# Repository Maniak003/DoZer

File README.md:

<!DOCTYPE html>
<html lang="en" data-color-mode="auto" data-light-theme="light" data-dark-theme="dark">
  <head>
    <meta charset="utf-8">
  </head>
    <body class="logged-in env-production page-responsive page-blob" style="word-wrap: break-word;">
      <a href="https://play.google.com/store/apps/details?id=ru.starline.dozer" rel="nofollow">Application download</a>
      <p> DoZer Scintillation gamma spectrometer based on SiPM Sensl FC60035/FJ60035, Broadcom AFBR-S4N66C013 & NaI(Tl) or SrI2(Eu).</p>
      
      <a href="https://github.com/Maniak003/DoZer/wiki/Description" rel="nofollow">Description</a>
    </body>
</html>

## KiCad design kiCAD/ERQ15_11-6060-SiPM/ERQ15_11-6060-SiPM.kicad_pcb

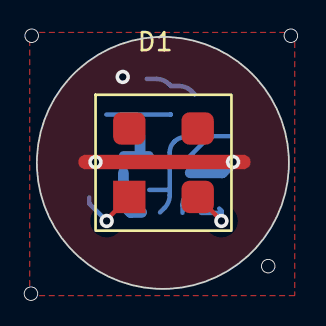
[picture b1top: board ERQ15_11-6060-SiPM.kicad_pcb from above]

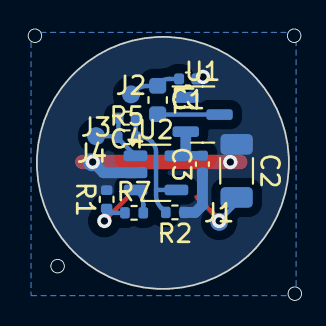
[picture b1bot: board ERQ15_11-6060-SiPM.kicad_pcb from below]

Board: 2 copper layers, 14.0 x 14.0 mm, 16 parts (15 on the bottom side), 9 nets.

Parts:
C1, C3: 10u; C_0402_1005Metric
C2: 10u; C_1206_3216Metric
C4: 2p; C_0402_1005Metric
D1: EQR15-11-6060D-S; EQR15_11-6060D-S
J1, J2, J3, J4: Conn; conn_mini
L1: 47uH; L_0603_1608Metric
R1: 1k; R_0402_1005Metric
R2, R7: 10k; R_0402_1005Metric
R5: 100k; R_0402_1005Metric
U1: MCP1700x-280xxTT; SOT-23
U2: OPA354; SOT-23-5

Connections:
+3V0: C3.2, U1.2 (VO), U2.5 (V+)
GND: C1.1, C2.1, C3.1, J4.1, R1.2, R2.1, U1.1 (GND), U2.2 (V-)
unnamed: C1.2, J2.1, L1.1
unnamed: C4.2, J3.1, R5.1, U2.1
unnamed: D1.2 (A), R1.1, R7.1
unnamed: C2.2, D1.1 (C), J1.1
unnamed: L1.2, U1.3 (VI)
unnamed: R7.2, U2.3 (+)
unnamed: C4.1, R2.2, R5.2, U2.4 (-)

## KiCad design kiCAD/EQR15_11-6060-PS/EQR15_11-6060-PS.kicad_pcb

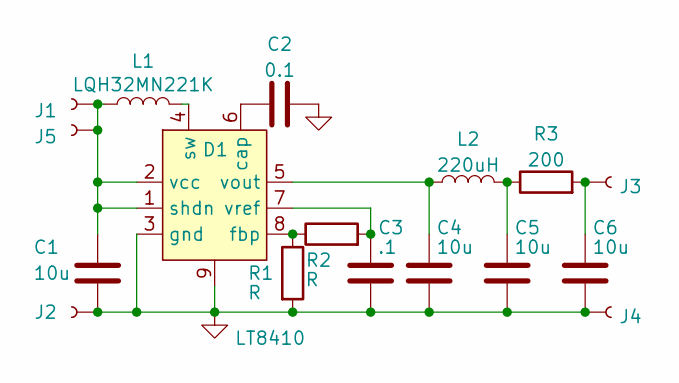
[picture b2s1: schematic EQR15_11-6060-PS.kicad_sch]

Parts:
C1: 10u; C_0402_1005Metric
C2: 0.1; C_0402_1005Metric
C3: .1; C_0402_1005Metric
C4, C5, C6: 10u; C_0805_2012Metric
D1: LT8410; DFN-8-1EP_2x2mm_P0.45mm_EP0.64x1.38mm
J1, J2, J3, J4, J5: Conn; conn_mini
L1: LQH32MN221K; L_1210_3225Metric
L2: 220uH; L_0805_2012Metric
R1, R2: R; R_0402_1005Metric
R3: 200; R_0402_1005Metric

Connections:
GND: C1.2, C2.2, C3.2, C4.2, C5.2, C6.2, D1.3 (gnd), D1.9, J2.1, J4.1, R1.2
unnamed: C1.1, D1.1 (shdn), D1.2 (vcc), J1.1, J5.1, L1.1
unnamed: C2.1, D1.6 (cap)
unnamed: C3.1, D1.7 (vref), R2.2
unnamed: C4.1, D1.5 (vout), L2.1
unnamed: C5.1, L2.2, R3.1
unnamed: C6.1, J3.1, R3.2
unnamed: D1.4 (sw), L1.2
unnamed: D1.8 (fbp), R1.1, R2.1

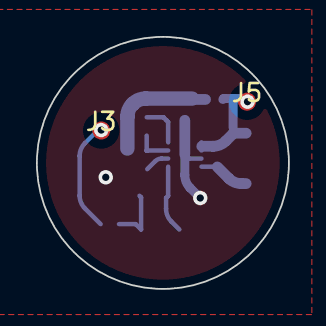
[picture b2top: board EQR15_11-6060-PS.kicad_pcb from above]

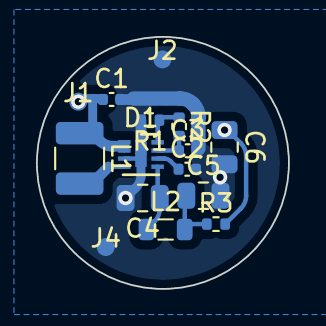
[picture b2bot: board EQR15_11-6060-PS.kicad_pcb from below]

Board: 2 copper layers, 14.0 x 14.0 mm, 17 parts (15 on the bottom side), 9 nets.

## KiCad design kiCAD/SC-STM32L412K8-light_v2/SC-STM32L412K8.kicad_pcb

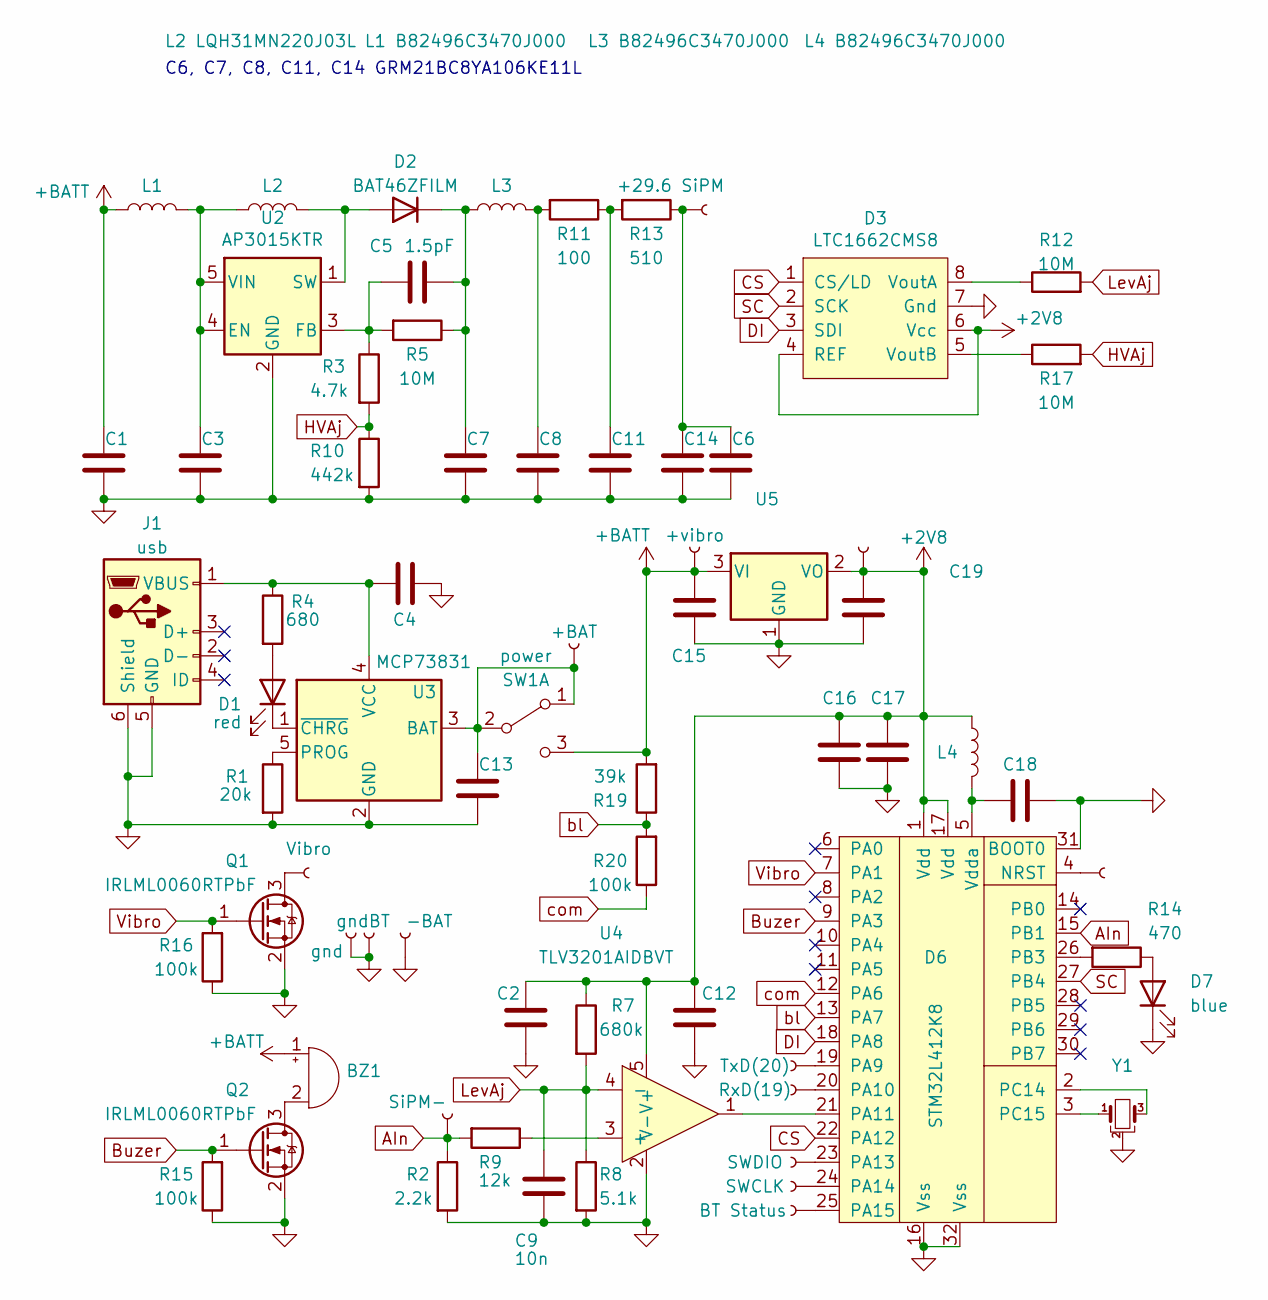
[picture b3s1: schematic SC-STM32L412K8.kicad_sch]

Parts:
BZ1: Buzzer; Buzzer5x5
C1, C2, C3, C4, C13, C15, C16, C17, C19: 1uF; C_0603_1608Metric
C5: 1.5pF; C_0603_1608Metric
C6, C7, C8, C11, C14: GRM21BC8YA106KE11L; C_0805_2012Metric
C9: 10n; C_0402_1005Metric
C12: GRM21BR60J226M; C_0805_2012Metric
C18: GRM21BR60J226M; C_0603_1608Metric
D1: red; LED_0402_1005Metric
D2: BAT46ZFILM; D_SOD-123
D3: LTC1662CMS8; MSOP-8_3x3mm_P0.65mm
D6: STM32L412K8; LQFP-32_7x7mm_P0.8mm
D7: blue; LED_0402_1005Metric
J1: usb; USB_Micro-B_Molex_47346-0001
J2: +29.6 SiPM; SMD-CONN
J3: TxD(20); conn_mini
J4: RxD(19); conn_mini
J5: SWDIO; conn_mini
J6: SWCLK; conn_mini
J7: +BAT; conn_mini
J8: SiPM-; SMD-CONN
J9: BT Status; conn_mini
J10: gnd; conn_mini
J11: Vibro; conn_mini
J12, J16: +2.8v; conn_mini
J13: +vibro; conn_mini
J14: gndBT; SMD-CONN
J15: -BAT; SMD-CONN
L1: L1 B82496C3470J000; L_0603_1608Metric
L2: L2 LQH31MN220J03L; L_1210_3225Metric
L3: L3 B82496C3470J000; L_0603_1608Metric
L4: L4 B82496C3470J000; L_0603_1608Metric
Q1, Q2: IRLML0060RTPbF; SOT-23
R1: 20k; R_0402_1005Metric
R2: 2.2k; R_0402_1005Metric
R3: 4.7k; R_0402_1005Metric
R4: 680; R_0402_1005Metric
R5: 10M; R_0603_1608Metric
R7: 680k; R_0402_1005Metric
R8: 5.1k; R_0402_1005Metric
R9: 12k; R_0402_1005Metric
R10: 442k; R_0402_1005Metric
R11: 100; R_0402_1005Metric
R12, R17: 10M; R_0402_1005Metric
R13: 510; R_0402_1005Metric
R14: 470; R_0402_1005Metric
R15, R16, R20: 100k; R_0402_1005Metric
R19: 39k; R_0603_1608Metric
SW1: power; MySwithc
U2: AP3015KTR; SOT-23-5
U3: MCP73831; TSOT-23-5
U4: TLV3201AIDBVT; SOT-23-5
U5: MCP1700-2802E; SOT-23
Y1: Crystal_GND2_Small; Resonator_SMD_Murata_CSTxExxV-3Pin_3.0x1.1mm

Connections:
+2V8: C2.1, C12.1, C16.1, C17.1, C19.1, D3.4 (REF), D3.6 (Vcc), D6.1 (Vdd), D6.17 (Vdd), J12.1, L4.1, R7.1, U4.5 (V+), U5.2 (VO)
+BATT: BZ1.1 (-), C1.2, C15.1, J13.1, L1.1, R19.2, SW1.3 (C), U5.3 (VI)
AIn: D6.15 (PB1), J8.1, R2.1, R9.2
Buzer: D6.9 (PA3), Q2.1 (G), R15.2
CS: D3.1 (CS/LD), D6.22 (PA12)
DI: D3.3 (SDI), D6.18 (PA8)
GND: C1.1, C2.2, C3.1, C4.1, C6.1, C7.1, C8.1, C9.2, C11.1, C12.2, C13.2, C14.1, C15.2, C16.2, C17.2, C18.1, C19.2, D3.7 (Gnd), D6.16 (Vss), D6.31 (BOOT0), D6.32 (Vss), D7.1 (K), J1.5 (GND), J1.6 (Shield), J10.1, J14.1, J15.1, Q1.2 (S), Q2.2 (S), R1.2, R2.2, R8.2, R10.2, R15.1, R16.1, U2.2 (GND), U3.2 (GND), U4.2 (V-), U5.1 (GND), Y1.2
HVAj: R3.2, R10.1, R17.2
LevAj: C9.1, R7.2, R8.1, R12.2, U4.4 (-)
unnamed: BZ1.2 (+), Q2.3 (D)
unnamed: C3.2, L1.2, L2.1, U2.4 (EN), U2.5 (VIN)
unnamed: C4.2, J1.1 (VBUS), R4.1, U3.4 (VCC)
unnamed: C5.1, C7.2, D2.1 (K), L3.1, R5.1
unnamed: C5.2, R3.1, R5.2, U2.3 (FB)
unnamed: C8.2, L3.2, R11.2
unnamed: C11.2, R11.1, R13.2
unnamed: C13.1, J7.1, SW1.1 (A), SW1.2 (B), U3.3 (BAT)
unnamed: C6.2, C14.2, J2.1, R13.1
unnamed: C18.2, D6.5 (Vdda), L4.2
unnamed: D1.1 (K), U3.1 (~CHRG)
unnamed: D1.2 (A), R4.2
unnamed: D2.2 (A), L2.2, U2.1 (SW)
unnamed: D3.5 (VoutB), R17.1
unnamed: D3.8 (VoutA), R12.1
unnamed: D6.2 (PC14), Y1.3
unnamed: D6.3 (PC15), Y1.1
unnamed: D6.4 (NRST), J16.1
unnamed: D6.19 (PA9), J3.1
unnamed: D6.20 (PA10), J4.1
unnamed: D6.21 (PA11), U4.1
unnamed: D6.23 (PA13), J5.1
unnamed: D6.24 (PA14), J6.1
unnamed: D6.25 (PA15), J9.1
unnamed: D6.26 (PB3), R14.2
unnamed: D7.2 (A), R14.1
unnamed: J11.1, Q1.3 (D)
unnamed: R1.1, U3.5 (PROG)
unnamed: R9.1, U4.3 (+)
SC: D3.2 (SCK), D6.27 (PB4)
Vibro: D6.7 (PA1), Q1.1 (G), R16.2
bl: D6.13 (PA7), R19.1, R20.2
com: D6.12 (PA6), R20.1

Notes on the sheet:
C6, C7, C8, C11, C14 GRM21BC8YA106KE11L

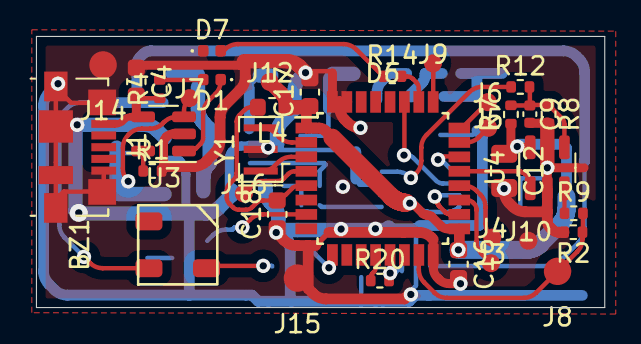
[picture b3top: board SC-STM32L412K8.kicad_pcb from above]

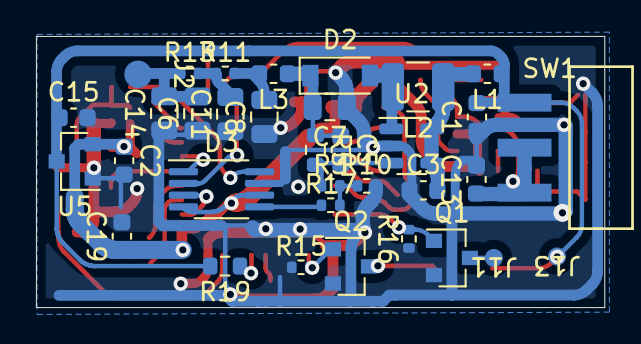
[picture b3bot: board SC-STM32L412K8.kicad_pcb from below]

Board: 2 copper layers, 31.6 x 15.1 mm, 70 parts (34 on the bottom side), 42 nets.

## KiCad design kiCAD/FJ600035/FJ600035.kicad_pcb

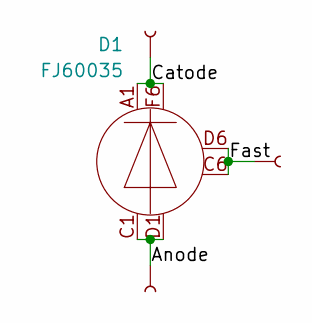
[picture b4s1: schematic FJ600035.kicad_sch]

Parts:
D1: FJ60035
J1, J2, J3: Conn; conn_mini

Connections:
/Anode: D1.C1, D1.D1, J2.1
/Catode: D1.A1, D1.F6, J1.1
/Fast: D1.C6, D1.D6, J3.1

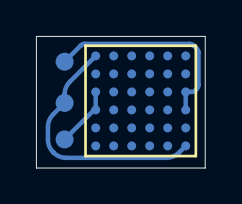
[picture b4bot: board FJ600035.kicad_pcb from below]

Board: 2 copper layers, 9.4 x 7.3 mm, 4 parts (4 on the bottom side), 3 nets.

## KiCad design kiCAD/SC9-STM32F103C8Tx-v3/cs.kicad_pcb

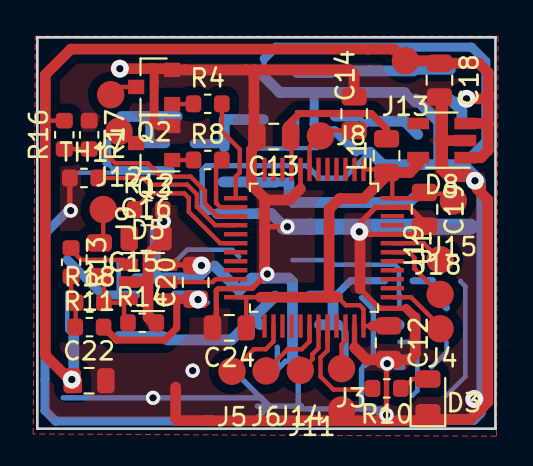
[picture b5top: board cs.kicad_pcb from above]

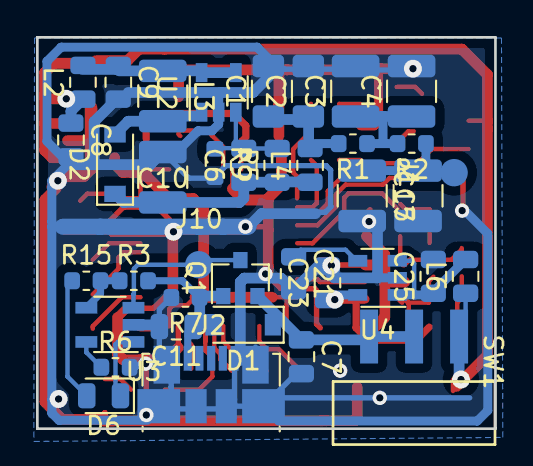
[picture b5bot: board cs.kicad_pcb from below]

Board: 2 copper layers, 25.5 x 21.7 mm, 80 parts (38 on the bottom side), 44 nets.

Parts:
C1, C2: .1uF; C_1206_3216Metric
C3, C4, C5, C10, C17: GRM32ER71H106K; C_1210_3225Metric
C6: 82pF; C_0805_2012Metric
C7, C8, C9, C11, C12, C13, C18, C19, C20, C22, C23, C24, C25: CL21A226MQQNNNE; C_0805_2012Metric
C14, C21: 0.1uF; C_0805_2012Metric
C15: 470pF; C_0805_2012Metric
C16: 10nF; C_0805_2012Metric
D1: MBR0520LT; D_SOD-123
D2: MBR0540LT; D_SOD-123
D3, D6: LED; LED_0805_2012Metric
D5: TLV3501; SOT-23-6
D8: NCP551SN; TSOT-23-5
J1: SiPM Catode(3) 29.6v; SMD-CONN
J2: USB_B_Micro; USB_Micro-B_Molex_47346-0001
J3: SWDIO; SMD-CONN
J4: SWCLK; SMD-CONN
J5: Stat; SMD-CONN
J6: TxD; SMD-CONN
J7: Vibro; SMD-CONN
J8: nRST; SMD-CONN
J9: SiPM Anode(1); SMD-CONN
J10: B+; SMD-CONN
J11: B-; SMD-CONN
J12: Buzzer; SMD-CONN
J13: +BAT; SMD-CONN
J14: RxD; SMD-CONN
J15: +BT; SMD-CONN
J18: I2C-SCL; SMD-CONN
J19: I2C-SDA; SMD-CONN
L1, L4, L6: 47uH; L_0805_2012Metric
L2: 10uH; L_0805_2012Metric
L3: B82422A1223K100; L_1210_3225Metric
Q1: IRLML5203; SOT-23
Q2, Q3: KT231; SOT-23
R1: 100; R_0603_1608Metric
R2, R10, R15: 1k; R_0603_1608Metric
R3: 1R; R_0603_1608Metric
R4, R7, R8, R16, R17: 10k; R_0603_1608Metric
R5: 300k; R_0805_2012Metric
R6: 20k; R_0603_1608Metric
R9: 13k; R_0603_1608Metric
R11: 100k; R_0603_1608Metric
R12: 2.2k; R_0603_1608Metric
R13: 4.7k; R_0603_1608Metric
R14: 12k; R_0603_1608Metric
R18: 220; R_0603_1608Metric
SW1: power; MySwithc
TH1: NCP18XH103F03RB; R_0603_1608Metric
U1: STM32F103C8Tx; LQFP-48_7x7mm_P0.5mm
U2: LM2733YMF; SOT-23-5
U3: LTC4054ES5-4.2; TSOT-23-5
U4: LP2985-3; SOT-23-5

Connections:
+3.3VA: C13.1, L1.2, U1.9
+3.3VADC: C20.1, C23.1, D5.4, R11.2, U4.5
+3V3: C12.1, C19.1, C24.1, D8.5, J15.1, L1.1, U1.1, U1.24, U1.36, U1.48
+5V: C8.1, C18.1, C22.1, D8.1, D8.3, J13.1, L2.1, L6.1, R16.2, SW1.3
GND: C1.2, C2.2, C3.2, C4.2, C5.2, C7.2, C8.2, C9.2, C10.2, C11.2, C12.2, C13.2, C14.2, C16.2, C17.2, C18.2, C19.2, C20.2, C21.2, C22.2, C23.2, C24.2, C25.2, D3.1, D5.2, D5.6, D8.2, J2.5, J2.6, J11.1, Q2.2, Q3.2, R6.2, R7.2, R9.2, R12.2, R14.2, R17.1, TH1.1, U1.8, U1.23, U1.35, U1.44, U1.47, U2.2, U3.2, U4.2
unnamed: C1.1, C2.1, L4.2, R1.2
unnamed: C3.1, C4.1, R1.1, R2.2
unnamed: C6.2, R5.2, R9.1, U2.3
unnamed: C7.1, D1.1, Q1.2, SW1.1, SW1.2
unnamed: C9.1, L2.2, L3.1, U2.4, U2.5
unnamed: C6.1, C10.1, D2.1, L4.1, R5.1
unnamed: C11.1, D1.2, J2.1, Q1.1, R3.2, R7.1
unnamed: C14.1, J8.1, U1.7
unnamed: C15.1, D5.3, R14.1, R18.2
unnamed: C15.2, J9.1, R12.1, U1.18
unnamed: C16.1, D5.1, R13.1
unnamed: C5.1, C17.1, J1.1, R2.1
unnamed: C21.1, U4.4
unnamed: C25.1, L6.2, U4.1, U4.3
unnamed: D2.2, L3.2, U2.1
unnamed: D3.2, R10.1
unnamed: J5.1, U1.26
unnamed: D5.5, U1.22
unnamed: D6.1, U3.1
unnamed: D6.2, R15.1
unnamed: J3.1, U1.34
unnamed: J4.1, U1.37
unnamed: J7.1, Q2.3
unnamed: J10.1, Q1.3, U3.3
unnamed: J12.1, Q3.3
unnamed: J18.1, U1.42
unnamed: J19.1, U1.43
unnamed: Q2.1, R4.1
unnamed: Q3.1, R8.1
unnamed: R4.2, U1.13
unnamed: R6.1, U3.5
unnamed: R8.2, U1.14
unnamed: R10.2, U1.32
unnamed: R11.1, R13.2, R18.1
unnamed: R3.1, R15.2, U3.4
unnamed: R16.1, R17.2, U1.15
unnamed: TH1.2, U1.16
uart_rxd: J14.1, U1.31
uart_txd: J6.1, U1.30

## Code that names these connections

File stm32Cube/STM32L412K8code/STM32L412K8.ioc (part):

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Mcu.Name=STM32L412K8Tx
Mcu.Package=LQFP32
Mcu.UserName=STM32L412K8Tx
PA1.GPIOParameters=GPIO_Label
PA1.GPIO_Label=Vibro
PA1.Signal=GPIO_Output
PA10.GPIOParameters=GPIO_Label
PA10.GPIO_Label=BT_RX
PA10.Mode=Asynchronous
PA10.Signal=USART1_RX
PA11.GPIOParameters=GPIO_Label
PA11.GPIO_Label=StartADC
PA11.Signal=GPXTI11
PA12.GPIOParameters=GPIO_Label
PA12.GPIO_Label=CS
PA12.Signal=GPIO_Output
PA15\ (JTDI).GPIOParameters=GPIO_Label
PA15\ (JTDI).GPIO_Label=BT_Status
PA15\ (JTDI).Signal=GPIO_Input
PA3.GPIOParameters=GPIO_Label
PA3.GPIO_Label=Buzzer
PA3.Signal=S_TIM2_CH4
PA6.GPIOParameters=PinState,GPIO_Label,GPIO_ModeDefaultOutputPP
PA6.GPIO_Label=COM
PA6.GPIO_ModeDefaultOutputPP=GPIO_MODE_OUTPUT_OD
PA6.PinState=GPIO_PIN_RESET
PA6.Signal=GPIO_Output
PA7.GPIOParameters=GPIO_Label
PA7.GPIO_Label=BAT_LEVEL
PA7.Signal=ADCx_IN12
PA8.Signal=GPIO_Output
PA9.GPIOParameters=GPIO_Label
PA9.GPIO_Label=BT_TX
PA9.Mode=Asynchronous
PA9.Signal=USART1_TX
PB1.GPIOParameters=GPIO_Label
PB1.GPIO_Label=SiPM
PB1.Signal=ADCx_IN16
PB3\ (JTDO/TRACESWO).GPIOParameters=GPIO_Label
PB3\ (JTDO/TRACESWO).GPIO_Label=LED
PB3\ (JTDO/TRACESWO).Signal=GPIO_Output
PB4\ (NJTRST).GPIOParameters=GPIO_Label
PB4\ (NJTRST).GPIO_Label=SC
PB4\ (NJTRST).Signal=GPIO_Output
RCC.HSE_VALUE=8000000
RCC.SYSCLKFreq_VALUE=15000000
RCC.SYSCLKSource=RCC_SYSCLKSOURCE_PLLCLK
board=custom

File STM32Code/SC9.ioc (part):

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Mcu.Name=STM32G031F(4-6-8)Px
Mcu.Package=TSSOP20
Mcu.UserName=STM32G031F8Px
PA1.Signal=GPIO_Input
PA11\ [PA9].Signal=GPXTI11
PA13.Mode=Serial_Wire
PA13.Signal=SYS_SWDIO
PA14-BOOT0.Mode=Serial_Wire
PA14-BOOT0.Signal=SYS_SWCLK
PA2.Mode=Asynchronous
PA2.Signal=USART2_TX
PA3.Mode=Asynchronous
PA3.Signal=USART2_RX
PA4.Mode=IN4
PA4.Signal=ADC1_IN4
PB8.Mode=I2C
PB8.Signal=I2C1_SCL
PB9.Mode=I2C
PB9.Signal=I2C1_SDA
PC15-OSC32_OUT\ (PC15).Signal=GPIO_Output
RCC.HSE_VALUE=8000000
RCC.SYSCLKFreq_VALUE=14000000
RCC.SYSCLKSource=RCC_SYSCLKSOURCE_PLLCLK
board=custom

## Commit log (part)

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2021-02-09 new file: AndroidStudio/BLE/.gitignore new file: AndroidStudio/BLE/.idea/codeStyles/Project.xml new file: AndroidStudio/BLE/.idea/compiler.xml new file: AndroidStudio/BLE/.idea/gradle.xml new file: A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
2021-02-09 modified: SC9-STM32F103C8Tx-v2/cs.kicad_pcb modified: SC9-STM32F103C8Tx-v2/cs.kicad_pcb-bak modified: SC9-STM32F103C8Tx-v2/cs.net modified: SC9-STM32F103C8Tx-v2/cs.sch modified: SC9-STM32F103C8Tx-v2/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
2021-02-10 STM32Code/.cproject STM32Code/.mxproject STM32Code/.project STM32Code/.settings/ STM32Code/Core/Inc/main.h STM32Code/Core/Inc/ssd1306.c STM32Code/Core/Inc/ssd1306.h STM32Code/Core/Inc/ssd1306_conf.h 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
2021-02-11 новый файл: SC9-STM32F103C8Tx-v3/README.md новый файл: SC9-STM32F103C8Tx-v3/bom/ibom.html новый файл: SC9-STM32F103C8Tx-v3/cs новый файл: SC9-STM32F103C8Tx-v3/cs-cache.lib новый файл: SC9-STM32F103C8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
2021-02-27 изменено: AndroidStudio/BLE/.idea/vcs.xml изменено: AndroidStudio/BLE/app/src/main/java/ru/starline/ble/MainActivity.java изменено: STM32Code/Release/SC4-LCD128x32.bin изменено: STM32Code/Release/SC4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
2021-03-01 modified: AndroidStudio/BLE/app/src/main/java/ru/starline/ble/MainActivity.java
2021-03-08 изменено: SC9-STM32F103C8Tx-v2/cs-cache.lib изменено: SC9-STM32F103C8Tx-v2/cs.sch изменено: SC9-STM32F103C8Tx-v2/cs.sch-bak изменено: STM32Code/.cproject изменено: STM32Code/.settings/language.settin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
2021-03-12 изменено: STM32Code/.settings/language.settings.xml изменено: STM32Code/Core/Inc/main.h изменено: STM32Code/Release/Core/Src/main.o изменено: STM32Code/Release/Core/Src/main.su изменено: STM32Code/Re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
2021-03-12 modified: SC-STM32L412K8/SC-STM32L412K8-cache.lib modified: SC-STM32L412K8/SC-STM32L412K8.kicad_pcb modified: SC-STM32L412K8/SC-STM32L412K8.kicad_pcb-bak modified: SC-STM32L412K8/SC-STM32L412K8.net m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
2021-03-14 изменено: STM32Code/Core/Inc/main.h изменено: STM32Code/Core/Src/main.c изменено: STM32Code/Release/Core/Src/main.o изменено: STM32Code/Release/Core/Src/main.su изменено: STM32Code/Release/Core/Src/s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
2021-03-17 изменено: AndroidStudio/BLE/app/src/main/java/ru/starline/ble/MainActivity.java изменено: STM32Code/.settings/language.settings.xml изменено: STM32Code/Core/Src/stm32f1xx_it.c изменено: STM32Code/Rel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
2021-03-19 Create LICENSE
2021-03-24 изменено: SC-STM32L412K8/SC-STM32L412K8.sch изменено: SC-STM32L412K8/SC-STM32L412K8.sch-bak
2021-03-30 modified: SC-STM32L412K8/SC-STM32L412K8.kicad_pcb modified: SC-STM32L412K8/SC-STM32L412K8.kicad_pcb-bak modified: SC-STM32L412K8/SC-STM32L412K8.net
2021-04-06 modified: STM32L412K8code/Core/Src/main.c modified: STM32L412K8code/Debug/Core/Src/main.o modified: STM32L412K8code/Debug/Core/Src/main.su modified: STM32L412K8code/Debug/STM32L412K8.bin modified: ST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
2021-04-07 modified: STM32L412K8code/.settings/language.settings.xml modified: STM32L412K8code/Core/Src/stm32l4xx_it.c modified: STM32L412K8code/Debug/Core/Src/main.o modified: STM32L412K8code/Debug/Core/Src/st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
2021-04-07 изменено: STM32L412K8code/.settings/language.settings.xml изменено: STM32L412K8code/Core/Inc/stm32l4xx_hal_conf.h изменено: STM32L412K8code/Core/Src/main.c изменено: STM32L412K8code/Core/Src/stm32l4x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
2021-04-10 изменено: AndroidStudio/BLE/app/src/main/java/ru/starline/ble/MainActivity.java изменено: STM32L412K8code/.settings/language.settings.xml изменено: STM32L412K8code/Core/Src/main.c изменено: STM32L412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
2021-04-11 изменено: STM32L412K8code/Core/Src/main.c
2021-04-18 новый файл: SC-STM32L412K8-light/SC-STM32L412K8-cache.lib новый файл: SC-STM32L412K8-light/SC-STM32L412K8-rescue.bck новый файл: SC-STM32L412K8-light/SC-STM32L412K8-rescue.dcm новый файл: SC-STM32L41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
2021-04-20 modified: FreeCAD/sc-box-7.FCStd modified: SC-STM32L412K8-light/SC-STM32L412K8.kicad_pcb modified: SC-STM32L412K8-light/SC-STM32L412K8.kicad_pcb-bak
2021-04-24 новый файл: AndroidDoZer/app/src/main/device.properties изменено: AndroidDoZer/app/src/main/java/ru/starline/dozer/FullscreenActivity.java
2021-04-25 изменено: AndroidDoZer/app/src/main/java/ru/starline/dozer/FullscreenActivity.java изменено: AndroidDoZer/app/src/main/res/layout/activity_fullscreen.xml
2021-04-26 new file: AndroidDoZer/app/src/main/res/drawable/ic_launcher_foreground.xml
2021-04-26 modified: AndroidDoZer/app/src/main/ic_launcher-playstore.png new file: AndroidDoZer/app/src/main/icons_vidro-playstore.png new file: AndroidDoZer/app/src/main/icons_vidro_wt-playstore.png new file: 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
2021-04-29 modified: AndroidDoZer/app/src/main/AndroidManifest.xml modified: AndroidDoZer/app/src/main/java/ru/starline/dozer/FullscreenActivity.java modified: AndroidDoZer/app/src/main/java/ru/starline/dozer/F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
2021-05-03 изменено: AndroidDoZer/app/src/main/java/ru/starline/dozer/FullscreenActivity.java изменено: STM32L412K8code/Core/Inc/main.h изменено: STM32L412K8code/Core/Src/main.c изменено: STM32L412K8code/Core/S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
2021-05-09 изменено: AndroidDoZer/app/src/main/java/ru/starline/dozer/FullscreenActivity.java изменено: AndroidDoZer/app/src/main/java/ru/starline/dozer/FullscreenActivity2.java изменено: STM32L412K8code/Core/I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
2021-05-22 новый файл: Documents/DoZer_JDY-19.png
2021-05-23 изменено: AndroidDoZer/app/build.gradle
2021-05-27 modified: AndroidDoZer/app/release/app-release.apk
2021-05-28 modified: AndroidDoZer/app/src/main/java/ru/starline/dozer/FullscreenActivity2.java
2021-05-31 modified: AndroidDoZer/app/release/app-release.apk modified: AndroidDoZer/app/src/main/java/ru/starline/dozer/FullscreenActivity.java modified: SC-STM32L412K8-light/SC-STM32L412K8-cache.lib modified: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
2021-06-04 modified: AndroidDoZer/app/release/app-release.apk modified: AndroidDoZer/app/src/main/java/ru/starline/dozer/FullscreenActivity.java
2021-06-07 modified: AndroidDoZer/app/release/app-release.apk modified: AndroidDoZer/app/src/main/java/ru/starline/dozer/FullscreenActivity.java modified: AndroidDoZer/app/src/main/java/ru/starline/dozer/Fullsc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
2021-06-07 new file: picture/Screenshot_20210607-130254.png
2021-06-08 modified: kiCAD/SC-STM32L412K8-light/SC-STM32L412K8.sch modified: kiCAD/SC-STM32L412K8-light/SC-STM32L412K8.sch-bak
2021-06-08 new file: picture/Screenshot_20210608-120211.png
2021-06-09 deleted: Documents/DoZer_SiPM.png modified: picture/DoZer_SiPM.png
2021-06-10 modified: Android/AndroidDoZer/app/release/app-release.apk modified: Android/AndroidDoZer/app/src/main/java/ru/starline/dozer/FullscreenActivity.java modified: Android/AndroidDoZer/app/src/main/java/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
2021-06-13 новый файл: picture/Screenshot_20210613-175320.png
2021-06-18 modified: stm32Cube/STM32L412K8code/Core/Inc/main.h modified: stm32Cube/STM32L412K8code/Core/Src/main.c modified: stm32Cube/STM32L412K8code/Core/Src/stm32l4xx_hal_msp.c modified: stm32Cube/STM32L412K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
2021-06-20 изменено: Android/AndroidDoZer/app/src/main/java/ru/starline/dozer/FullscreenActivity.java изменено: Android/AndroidDoZer/app/src/main/res/values/strings.xml изменено: kiCAD/SC-STM32L412K8-light/SC-S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
2021-06-27 изменено: picture/SC-STM32L412K8.png
2021-07-02 modified: kiCAD/SC-STM32L412K8-light/SC-STM32L412K8.kicad_pcb modified: kiCAD/SC-STM32L412K8-light/SC-STM32L412K8.kicad_pcb-bak
2021-07-05 new file: picture/Screenshot_20210704-132631.png
2021-07-16 modified: Android/AndroidDoZer/app/release/app-release.apk modified: Android/AndroidDoZer/app/src/main/java/ru/starline/dozer/FullscreenActivity.java modified: Android/AndroidDoZer/app/src/main/res/l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
2021-07-23 изменено: kiCAD/FJ600035/FJ600035-cache.lib изменено: kiCAD/FJ600035/FJ600035.kicad_pcb изменено: kiCAD/FJ600035/FJ600035.kicad_pcb-bak изменено: kiCAD/FJ600035/FJ600035.sch изменено: kiCAD/FJ600035/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
2021-09-12 новый файл: Documents/FSC-BT691+Datasheet+V1.2+EN.pdf новый файл: Documents/FSC-BT6XX+Programming+User+Guide+V3.0(BLE).pdf
2021-09-13 new file: picture/Screenshot_20210913-154949.png
2021-09-24 modified: kiCAD/SC-STM32L412K8-light/SC-STM32L412K8.sch-bak
2021-09-26 удалено: kiCAD/SC-STM32L412K8-light/bom/ibom.html новый файл: kiCAD/SC-STM32L412K8-light/bom/ibom.html.gz
2021-09-30 deleted: Android/AndroidDoZer/app/build/outputs/apk/release/app-release.apk
2021-10-11 new file: picture/IMG_20211010_180026.jpg new file: picture/Screenshot_20210606-123445.png new file: picture/Screenshot_20211011-080527.png
2021-10-12 изменено: stm32Cube/STM32L412K8code/.mxproject изменено: stm32Cube/STM32L412K8code/.settings/language.settings.xml изменено: stm32Cube/STM32L412K8code/Debug/Core/Src/main.o изменено: stm32Cube/STM32L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
2021-10-17 изменено: stm32Cube/STM32L412K8code/Core/Src/main.c изменено: stm32Cube/STM32L412K8code/Core/Src/stm32l4xx_it.c изменено: stm32Cube/STM32L412K8code/Release/Core/Src/main.o изменено: stm32Cube/STM32L4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
2021-10-24 изменено: stm32Cube/STM32L412K8code/.settings/language.settings.xml изменено: stm32Cube/STM32L412K8code/Core/Src/main.c изменено: stm32Cube/STM32L412K8code/Release/Core/Src/main.o изменено: stm32Cube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
2021-10-30 изменено: kiCAD/SC-STM32L412K8-light/SC-STM32L412K8.sch изменено: kiCAD/SC-STM32L412K8-light/SC-STM32L412K8.sch-bak изменено: kiCAD/SC-STM32L412K8-light/bom/ibom.html.gz
2021-11-03 изменено: kiCAD/SC-STM32L412K8-light/SC-STM32L412K8.kicad_pcb-bak
2021-11-08 изменено: Android/AndroidDoZer/.idea/misc.xml
2021-11-24 изменено: kiCAD/SC-STM32L412K8-light/bom/ibom.html.gz
2021-12-08 изменено: Documents/isotops.list
2022-04-10 изменено: stm32Cube/STM32L412K8code/Release/makefile
2022-09-15 изменено: Release/all.zip изменено: Release/mk.sh
2022-10-17 изменено: Release/all.zip изменено: kiCAD/SC-STM32L412K8-light/SC-STM32L412K8.kicad_pcb изменено: kiCAD/SC-STM32L412K8-light/SC-STM32L412K8.kicad_pcb-bak
2022-10-20 изменено: stm32Cube/STM32L412K8code/.cproject изменено: stm32Cube/STM32L412K8code/.mxproject изменено: stm32Cube/STM32L412K8code/.project изменено: stm32Cube/STM32L412K8code/.settings/language.settin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
2022-11-30 изменено: Android/AndroidDoZer/app/src/main/AndroidManifest.xml изменено: Android/AndroidDoZer/app/src/main/java/ru/starline/dozer/FullscreenActivity.java изменено: Android/AndroidDoZer/app/src/main/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
2023-03-03 новый файл: picture/2023_03_03_14_29_00_972.png новый файл: picture/2023_03_03_14_31_07_471.png новый файл: picture/IMG_20230303_142326.jpg новый файл: picture/IMG_20230303_142428.jpg новый файл: pic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
2023-03-06 новый файл: picture/Screenshot_20230306-181206.png
2023-06-14 новый файл: Documents/GM-energy-comp.pdf
2023-07-15 Bundle v1.3
2023-08-27 изменено: STM32L412K8code/.cproject изменено: STM32L412K8code/.mxproject изменено: STM32L412K8code/.settings/language.settings.xml изменено: STM32L412K8code/Core/Inc/main.h изменено: STM32L412K8code/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
2023-09-12 удалено: kiCAD/SC-STM32L412K8-light_v2/SC-STM32L412K8-backups/SC-STM32L412K8-2023-09-11_154928.zip изменено: kiCAD/SC-STM32L412K8-light_v2/SC-STM32L412K8.kicad_pcb изменено: kiCAD/SC-STM32L412K8-ligh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
2023-10-14 новый файл: Documents/DoZer-current.png новый файл: Documents/LT8410-current.png изменено: kiCAD/EQR15_11-6060-PS/EQR15_11-6060-PS.kicad_pcb изменено: kiCAD/EQR15_11-6060-PS/EQR15_11-6060-PS.kicad_sch
2024-03-26 Android 13 support
2024-03-29 Android 13, 14
